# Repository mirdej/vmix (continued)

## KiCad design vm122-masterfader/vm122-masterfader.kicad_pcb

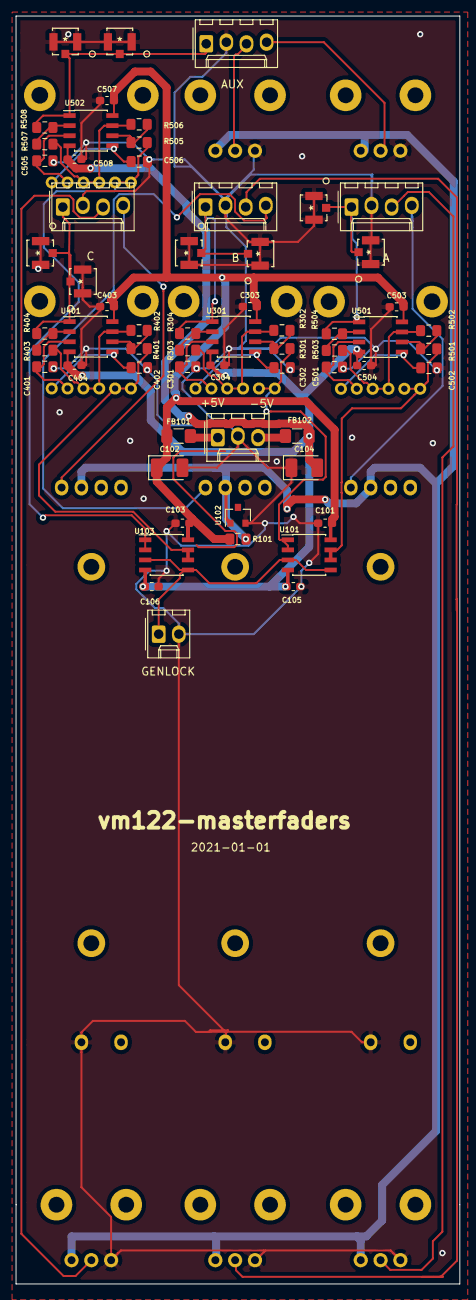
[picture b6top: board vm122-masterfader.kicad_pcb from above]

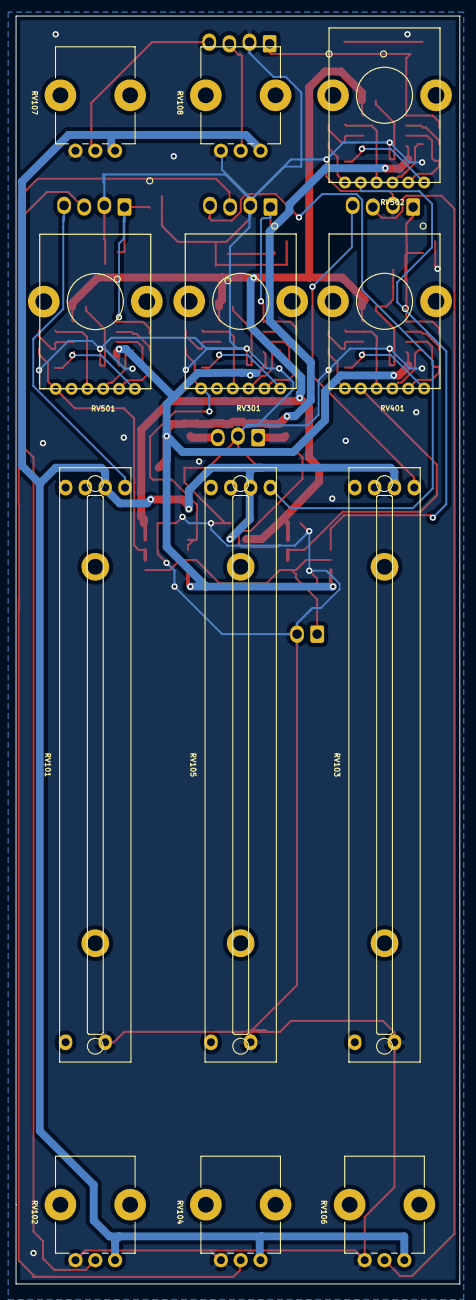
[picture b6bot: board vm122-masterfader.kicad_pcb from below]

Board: 2 copper layers, 56.0 x 160.0 mm, 74 parts (12 on the bottom side), 43 nets.

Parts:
C101, C103, C105, C106, C303, C304, C403, C404, C503, C504, C507, C508: 100n; C_0603_1608Metric_Pad1.05x0.95mm_HandSolder
C102, C104: CP; CP_EIA-3528-21_Kemet-B_Pad1.50x2.35mm_HandSolder
C301, C302, C401, C402, C501, C502, C505, C506: 10p; C_0805_2012Metric_Pad1.15x1.40mm_HandSolder
FB101, FB102: Ferrite_Bead; L_1206_3216Metric_Pad1.42x1.75mm_HandSolder
J101: Conn_01x03; Molex_KK-254_AE-6410-03A_1x03_P2.54mm_Vertical
J102: GENLOCK; Molex_KK-254_AE-6410-02A_1x02_P2.54mm_Vertical
J103: A; Molex_KK-254_AE-6410-04A_1x04_P2.54mm_Vertical
J104: B; Molex_KK-254_AE-6410-04A_1x04_P2.54mm_Vertical
J105: C; Molex_KK-254_AE-6410-04A_1x04_P2.54mm_Vertical
J106: D; Molex_KK-254_AE-6410-04A_1x04_P2.54mm_Vertical
J201, J202, J301, J302, J401, J402, J501, J502: UMCC; TE_UMCC_2337019-1
R101: 560; R_0805_2012Metric_Pad1.15x1.40mm_HandSolder
R301, R302, R303, R304, R401, R402, R403, R404, R501, R502, R503, R504, R505, R506, R507, R508: 220; R_0805_2012Metric_Pad1.15x1.40mm_HandSolder
RV101, RV103, RV105: SCALE; Potentiometer_Alps_RS6011xP_Slide
RV102, RV104, RV106, RV108: BIAS; Potentiometer_Alps_RK09K_Single_Vertical
RV107: SCALE; Potentiometer_Alps_RK09K_Single_Vertical
RV301, RV401, RV501, RV502: R_POT_Dual; RK12L123
U101, U103, U301, U401, U501, U502: LMH6643; SOIC-8_3.9x4.9mm_P1.27mm
U102: ADR510; SOT-23

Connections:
+5V: C101.1, C102.1, C103.1, C303.2, C403.2, C503.2, C507.2, FB101.1, R101.1, U101.8, U103.8, U301.8, U401.8, U501.8, U502.8
-5V: C104.2, C105.1, C106.1, C304.1, C404.1, C504.1, C508.1, FB102.1, U101.4, U103.4, U301.4, U401.4, U501.4, U502.4
/Phase1/INPUT: R501.2, RV501.1, RV501.2, U101.6, U101.7
/Phase1/OUTPUT: J103.1, J201.1, J202.1, R504.1, U501.1
/sheet5FF0F8E5/INPUT: R401.2, RV401.1, RV401.2, U103.6, U103.7
/sheet5FF0F8E5/OUTPUT: J105.1, J401.1, J402.1, R404.1, U401.1
/sheet5FF0F40B/INPUT: R301.2, RV301.1, RV301.2, U101.1, U101.2
/sheet5FF0F40B/OUTPUT: J104.1, J301.1, J302.1, R304.1, U301.1
/sheet5FF0F904/INPUT: R505.2, RV502.1, RV502.2, U103.1, U103.2
/sheet5FF0F904/OUTPUT: J106.1, J501.1, J502.1, R508.1, U502.1
GND: C101.2, C102.2, C103.2, C104.1, C105.2, C106.2, C301.2, C302.2, C303.1, C304.2, C401.2, C402.2, C403.1, C404.2, C501.2, C502.2, C503.1, C504.2, C505.2, C506.2, C507.1, C508.2, J101.2, J102.2, J103.2, J104.2, J105.2, J106.2, J201.2, J201.3, J202.2, J202.3, J301.2, J301.3, J302.2, J302.3, J401.2, J401.3, J402.2, J402.3, J501.2, J501.3, J502.2, J502.3, RV101.3, RV102.3, RV103.3, RV104.3, RV105.3, RV106.3, RV107.3, RV108.3, U102.2
unnamed: C301.1, RV301.6, U301.3
unnamed: C302.1, RV301.3, U301.5
unnamed: C401.1, RV401.6, U401.3
unnamed: C402.1, RV401.3, U401.5
unnamed: C501.1, RV501.6, U501.3
unnamed: C502.1, RV501.3, U501.5
unnamed: C505.1, RV502.6, U502.3
unnamed: C506.1, RV502.3, U502.5
unnamed: FB101.2, J101.1
unnamed: FB102.2, J101.3
unnamed: J102.1, U101.3, U101.5, U103.3, U103.5
unnamed: J103.3, RV102.2
unnamed: J103.4, RV101.2
unnamed: J104.3, RV104.2
unnamed: J104.4, RV105.2
unnamed: J105.3, RV106.2
unnamed: J105.4, RV103.2
unnamed: J106.3, RV108.2
unnamed: J106.4, RV107.2
unnamed: R301.1, R302.2, U301.6
unnamed: R302.1, R303.2, RV301.4, RV301.5, U301.7
unnamed: R303.1, R304.2, U301.2
unnamed: R401.1, R402.2, U401.6
unnamed: R402.1, R403.2, RV401.4, RV401.5, U401.7
unnamed: R403.1, R404.2, U401.2
unnamed: R501.1, R502.2, U501.6
unnamed: R502.1, R503.2, RV501.4, RV501.5, U501.7
unnamed: R503.1, R504.2, U501.2
unnamed: R505.1, R506.2, U502.6
unnamed: R506.1, R507.2, RV502.4, RV502.5, U502.7
unnamed: R507.1, R508.2, U502.2
VCCQ: R101.2, RV101.1, RV102.1, RV103.1, RV104.1, RV105.1, RV106.1, RV107.1, RV108.1, U102.1

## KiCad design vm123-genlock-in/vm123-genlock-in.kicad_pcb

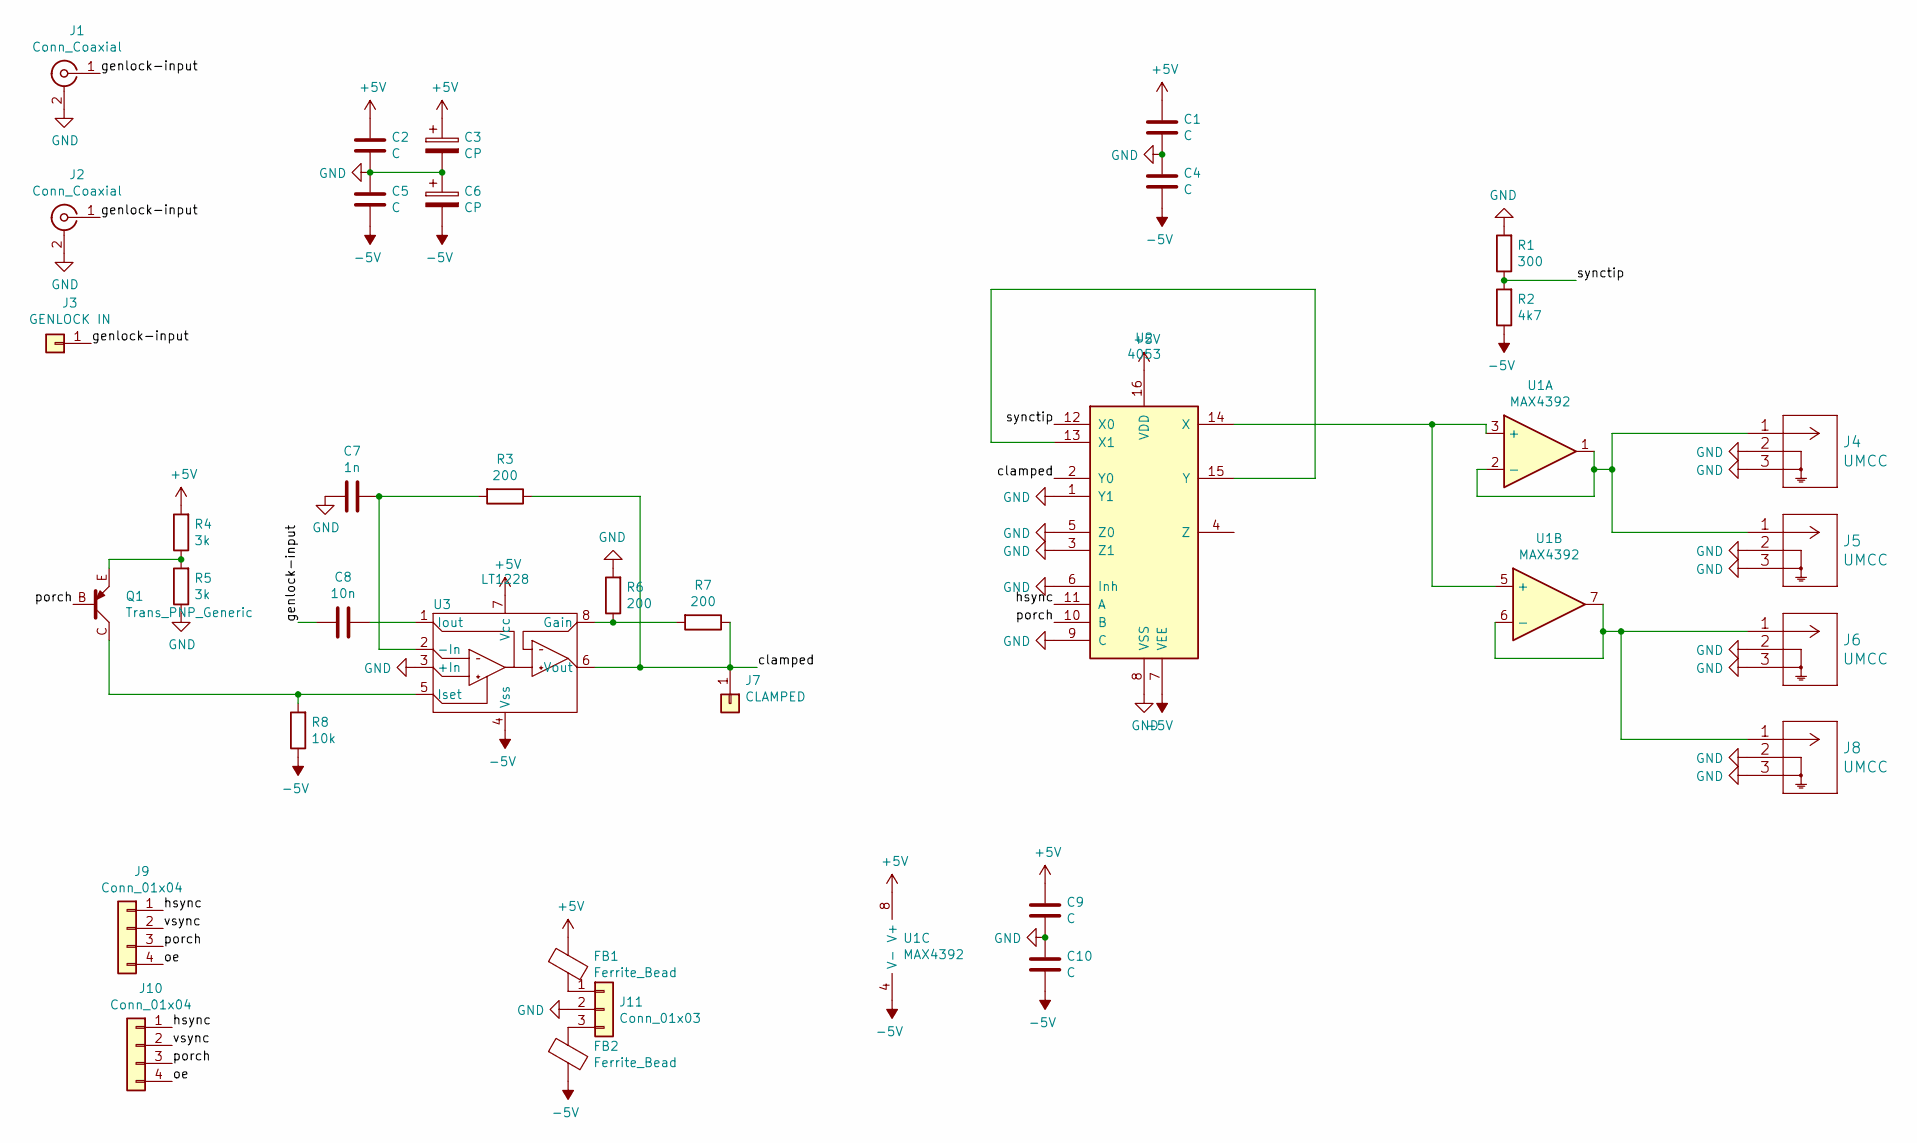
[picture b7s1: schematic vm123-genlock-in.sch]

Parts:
C1, C2, C4, C5, C9, C10: C; C_0603_1608Metric_Pad1.05x0.95mm_HandSolder
C3, C6: CP; CP_EIA-3528-21_Kemet-B_Pad1.50x2.35mm_HandSolder
C7: 1n; C_1206_3216Metric_Pad1.42x1.75mm_HandSolder
C8: 10n; C_1206_3216Metric_Pad1.42x1.75mm_HandSolder
FB1, FB2: Ferrite_Bead; L_1206_3216Metric_Pad1.42x1.75mm_HandSolder
J1, J2: Conn_Coaxial; BNC_MOLEX_0731000080_Horizontal
J3: GENLOCK IN; Solderpad_1mm
J4, J5, J6, J8: UMCC; TE_UMCC_2337019-1
J7: CLAMPED; Solderpad_1mm
J9, J10: Conn_01x04; Molex_KK-254_AE-6410-04A_1x04_P2.54mm_Vertical
J11: Conn_01x03; PinHeader_1x03_P2.54mm_Vertical
Q1: Trans_PNP_Generic; SOT-23_BEC
R1: 300; R_0805_2012Metric_Pad1.15x1.40mm_HandSolder
R2: 4k7; R_0805_2012Metric_Pad1.15x1.40mm_HandSolder
R3, R6, R7: 200; R_0805_2012Metric_Pad1.15x1.40mm_HandSolder
R4, R5: 3k; R_0805_2012Metric_Pad1.15x1.40mm_HandSolder
R8: 10k; R_0805_2012Metric_Pad1.15x1.40mm_HandSolder
U1: MAX4392; SOIC-8_3.9x4.9mm_P1.27mm
U2: 4053; SOIC-16_3.9x9.9mm_P1.27mm
U3: LT1228; SOIC-8_3.9x4.9mm_P1.27mm

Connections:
+5V: C1.1, C2.1, C3.1, C9.1, FB1.1, R4.2, U1.8 (V+), U2.16 (VDD), U3.7 (Vcc)
-5V: C4.2, C5.2, C6.2, C10.2, FB2.2, R2.1, R8.1, U1.4 (V-), U2.7 (VEE), U3.4 (Vss)
/clamped: J7.1, R3.1, R7.1, U2.2 (Y0), U3.6 (Vout)
/genlock-input: C8.2, J1.1 (In), J2.1 (In), J3.1
/hsync: J9.1, J10.1, U2.11 (A)
/oe: J9.4, J10.4
/porch: J9.3, J10.3, Q1.B, U2.10 (B)
/synctip: R1.1, R2.2, U2.12 (X0)
/vsync: J9.2, J10.2
GND: C1.2, C2.2, C3.2, C4.1, C5.1, C6.1, C7.2, C9.2, C10.1, J1.2 (Ext), J2.2 (Ext), J4.2, J4.3, J5.2, J5.3, J6.2, J6.3, J8.2, J8.3, J11.2, R1.2, R5.1, R6.2, U2.1 (Y1), U2.3 (Z1), U2.5 (Z0), U2.6 (Inh), U2.8 (VSS), U2.9 (C), U3.3 (+In)
unnamed: C7.1, R3.2, U3.2 (-In)
unnamed: C8.1, U3.1 (Iout)
unnamed: FB1.2, J11.1
unnamed: FB2.1, J11.3
unnamed: J4.1, J5.1, U1.1, U1.2 (-)
unnamed: J6.1, J8.1, U1.6 (-), U1.7
unnamed: Q1.C, R8.2, U3.5 (Iset)
unnamed: Q1.E, R4.1, R5.2
unnamed: R6.1, R7.2, U3.8 (Gain)
unnamed: U1.3 (+), U1.5 (+), U2.14 (X)
unnamed: U2.13 (X1), U2.15 (Y)

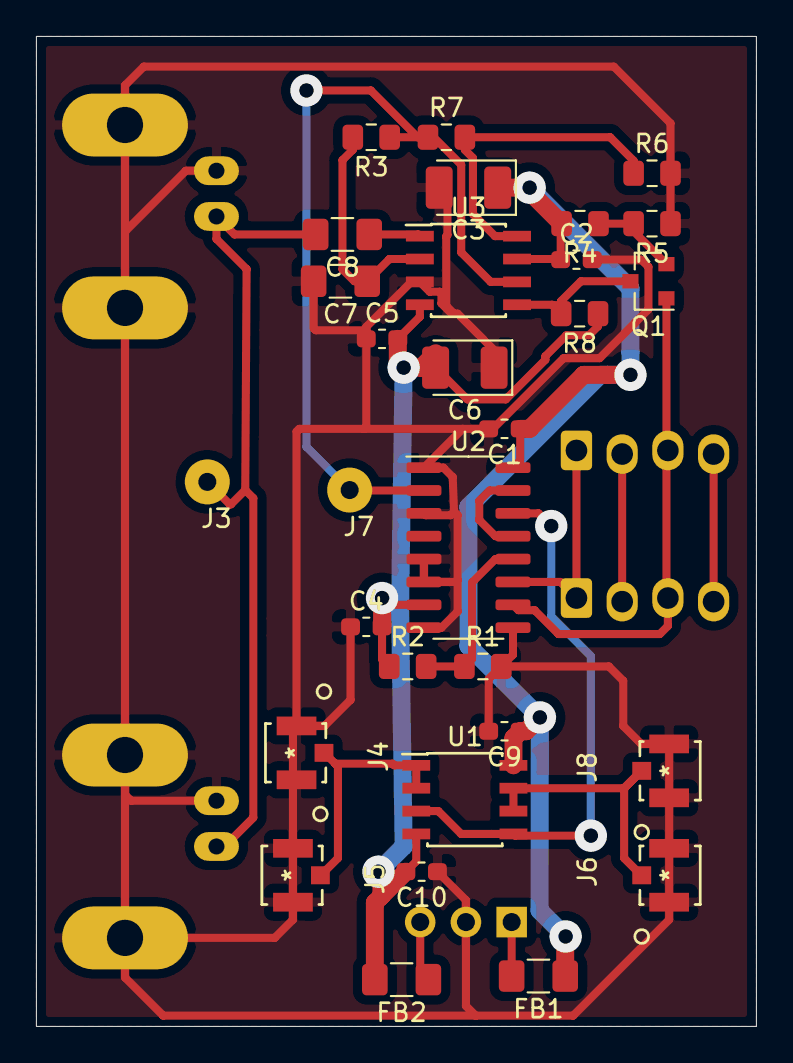
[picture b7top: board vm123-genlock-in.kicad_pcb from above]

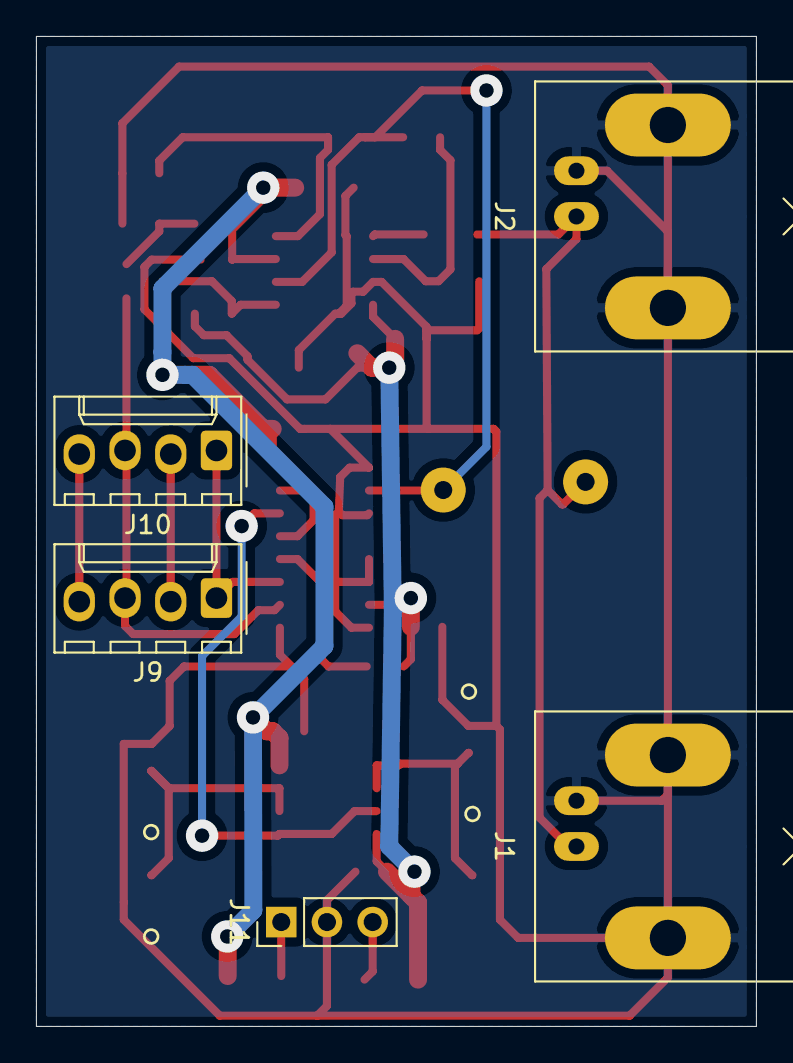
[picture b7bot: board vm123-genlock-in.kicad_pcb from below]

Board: 2 copper layers, 40.0 x 55.0 mm, 35 parts (5 on the bottom side), 21 nets.

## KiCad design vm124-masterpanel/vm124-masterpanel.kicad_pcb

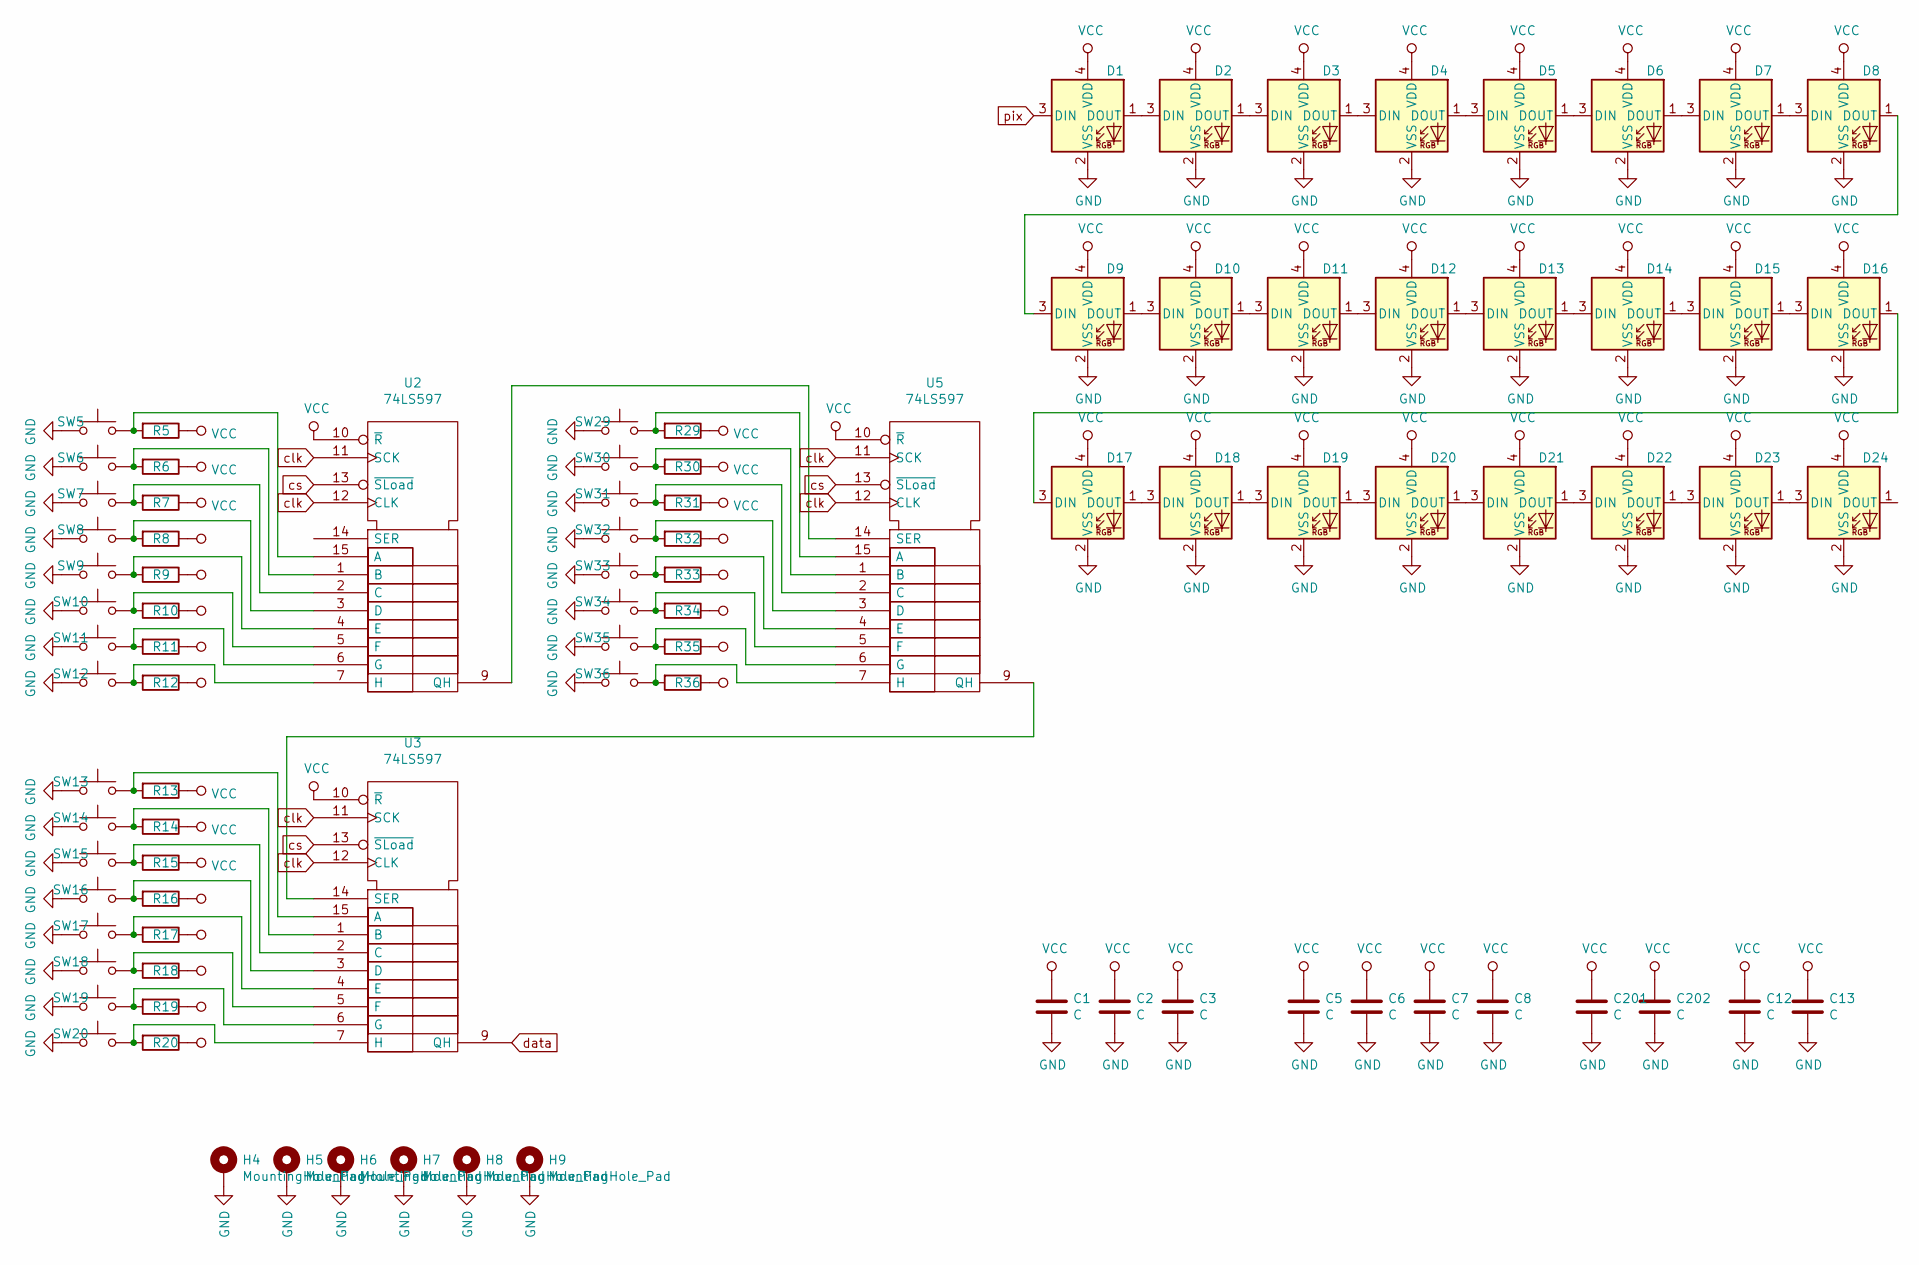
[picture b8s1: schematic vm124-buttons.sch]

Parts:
C1, C2, C3, C5, C6, C7, C8, C12, C13, C201, C202: C; C_0603_1608Metric_Pad1.05x0.95mm_HandSolder
D1, D2, D3, D4, D5, D6, D7, D8, D9, D10, D11, D12, D13, D14, D15, D16, D17, D18, D19, D20, D21, D22, D23, D24: SK6812MINI; LED_SK6812MINI_PLCC4_3.5x3.5mm_P1.75mm
H4, H5, H6, H7, H8, H9: MountingHole_Pad; MountingHole_3.2mm_M3_DIN965_Pad
R5, R6, R7, R8, R9, R10, R11, R12, R13, R14, R15, R16, R17, R18, R19, R20, R29, R30, R31, R32, R33, R34, R35, R36: R; R_0805_2012Metric_Pad1.15x1.40mm_HandSolder
SW5, SW6, SW7, SW8, SW9, SW10, SW11, SW12, SW13, SW14, SW15, SW16, SW17, SW18, SW19, SW20, SW29, SW30, SW31, SW32, SW33, SW34, SW35, SW36: SW_Push; Alps_Tactile_Switch
U2, U3, U5: 74LS597; SOP-16_4.4x10.4mm_P1.27mm

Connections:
GND: C1.2, C2.2, C3.2, C5.2, C6.2, C7.2, C8.2, C12.2, C13.2, C201.2, C202.2, D1.2 (VSS), D2.2 (VSS), D3.2 (VSS), D4.2 (VSS), D5.2 (VSS), D6.2 (VSS), D7.2 (VSS), D8.2 (VSS), D9.2 (VSS), D10.2 (VSS), D11.2 (VSS), D12.2 (VSS), D13.2 (VSS), D14.2 (VSS), D15.2 (VSS), D16.2 (VSS), D17.2 (VSS), D18.2 (VSS), D19.2 (VSS), D20.2 (VSS), D21.2 (VSS), D22.2 (VSS), D23.2 (VSS), D24.2 (VSS), H4.1, H5.1, H6.1, H7.1, H8.1, H9.1, SW5.1, SW6.1, SW7.1, SW8.1, SW9.1, SW10.1, SW11.1, SW12.1, SW13.1, SW14.1, SW15.1, SW16.1, SW17.1, SW18.1, SW19.1, SW20.1, SW29.1, SW30.1, SW31.1, SW32.1, SW33.1, SW34.1, SW35.1, SW36.1, U2.8 (GND), U3.8 (GND), U5.8 (GND); also elsewhere on the board
unnamed: D1.1 (DOUT), D2.3 (DIN)
unnamed: D2.1 (DOUT), D3.3 (DIN)
unnamed: D3.1 (DOUT), D4.3 (DIN)
unnamed: D4.1 (DOUT), D5.3 (DIN)
unnamed: D5.1 (DOUT), D6.3 (DIN)
unnamed: D6.1 (DOUT), D7.3 (DIN)
unnamed: D7.1 (DOUT), D8.3 (DIN)
unnamed: D8.1 (DOUT), D9.3 (DIN)
unnamed: D10.1 (DOUT), D11.3 (DIN)
unnamed: D9.1 (DOUT), D10.3 (DIN)
unnamed: D11.1 (DOUT), D12.3 (DIN)
unnamed: D12.1 (DOUT), D13.3 (DIN)
unnamed: D13.1 (DOUT), D14.3 (DIN)
unnamed: D14.1 (DOUT), D15.3 (DIN)
unnamed: D15.1 (DOUT), D16.3 (DIN)
unnamed: D16.1 (DOUT), D17.3 (DIN)
unnamed: D17.1 (DOUT), D18.3 (DIN)
unnamed: D18.1 (DOUT), D19.3 (DIN)
unnamed: D19.1 (DOUT), D20.3 (DIN)
unnamed: D20.1 (DOUT), D21.3 (DIN)
unnamed: D21.1 (DOUT), D22.3 (DIN)
unnamed: D22.1 (DOUT), D23.3 (DIN)
unnamed: D23.1 (DOUT), D24.3 (DIN)
unnamed: R5.2, SW5.2, U2.15 (A)
unnamed: R6.2, SW6.2, U2.1 (B)
unnamed: R7.2, SW7.2, U2.2 (C)
unnamed: R8.2, SW8.2, U2.3 (D)
unnamed: R9.2, SW9.2, U2.4 (E)
unnamed: R10.2, SW10.2, U2.5 (F)
unnamed: R11.2, SW11.2, U2.6 (G)
unnamed: R12.2, SW12.2, U2.7 (H)
unnamed: R13.2, SW13.2, U3.15 (A)
unnamed: R14.2, SW14.2, U3.1 (B)
unnamed: R15.2, SW15.2, U3.2 (C)
unnamed: R16.2, SW16.2, U3.3 (D)
unnamed: R17.2, SW17.2, U3.4 (E)
unnamed: R18.2, SW18.2, U3.5 (F)
unnamed: R19.2, SW19.2, U3.6 (G)
unnamed: R20.2, SW20.2, U3.7 (H)
unnamed: R29.2, SW29.2, U5.15 (A)
unnamed: R30.2, SW30.2, U5.1 (B)
unnamed: R31.2, SW31.2, U5.2 (C)
unnamed: R32.2, SW32.2, U5.3 (D)
unnamed: R33.2, SW33.2, U5.4 (E)
unnamed: R34.2, SW34.2, U5.5 (F)
unnamed: R35.2, SW35.2, U5.6 (G)
unnamed: R36.2, SW36.2, U5.7 (H)
unnamed: U2.9 (QH), U5.14 (SER)
unnamed: U3.14 (SER), U5.9 (QH)
VCC: C1.1, C2.1, C3.1, C5.1, C6.1, C7.1, C8.1, C12.1, C13.1, C201.1, C202.1, D1.4 (VDD), D2.4 (VDD), D3.4 (VDD), D4.4 (VDD), D5.4 (VDD), D6.4 (VDD), D7.4 (VDD), D8.4 (VDD), D9.4 (VDD), D10.4 (VDD), D11.4 (VDD), D12.4 (VDD), D13.4 (VDD), D14.4 (VDD), D15.4 (VDD), D16.4 (VDD), D17.4 (VDD), D18.4 (VDD), D19.4 (VDD), D20.4 (VDD), D21.4 (VDD), D22.4 (VDD), D23.4 (VDD), D24.4 (VDD), R5.1, R6.1, R7.1, R8.1, R9.1, R10.1, R11.1, R12.1, R13.1, R14.1, R15.1, R16.1, R17.1, R18.1, R19.1, R20.1, R29.1, R30.1, R31.1, R32.1, R33.1, R34.1, R35.1, R36.1, U2.10 (~R), U2.16 (VCC), U3.10 (~R), U3.16 (VCC), U5.10 (~R), U5.16 (VCC); also elsewhere on the board
clk: U2.11 (SCK), U2.12 (CLK), U3.11 (SCK), U3.12 (CLK), U5.11 (SCK), U5.12 (CLK); also elsewhere on the board
cs: U2.13 (~SLoad), U3.13 (~SLoad), U5.13 (~SLoad); also elsewhere on the board
data: U3.9 (QH); also elsewhere on the board
pix: D1.3 (DIN); also elsewhere on the board

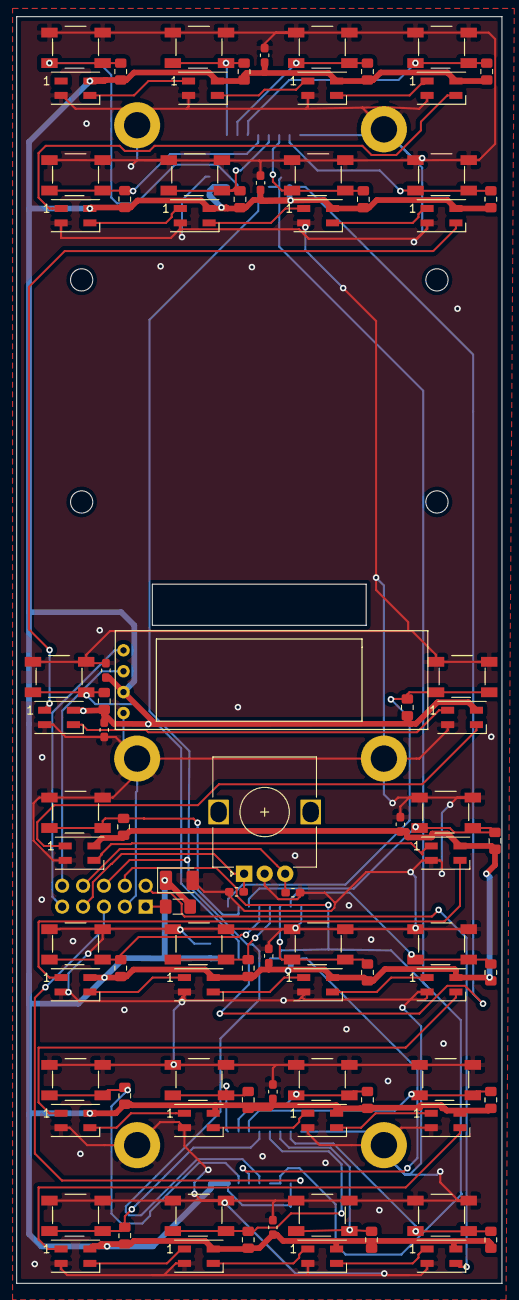
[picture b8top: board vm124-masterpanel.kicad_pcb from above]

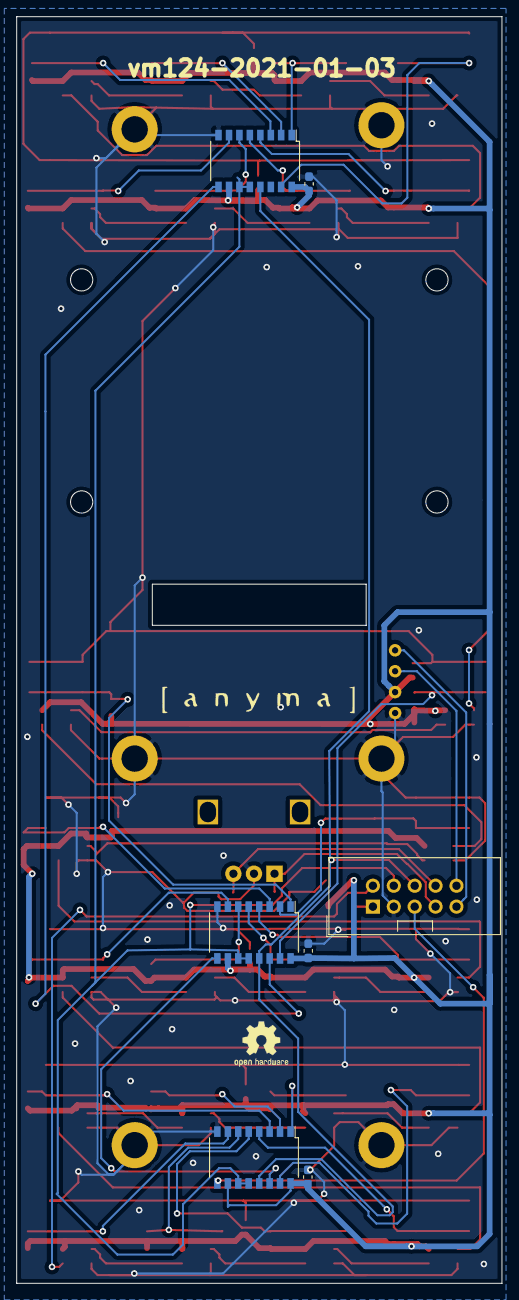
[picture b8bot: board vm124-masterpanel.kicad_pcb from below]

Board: 2 copper layers, 59.0 x 154.0 mm, 105 parts (9 on the bottom side), 60 nets.

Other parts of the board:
C101: CP; CP_EIA-3528-21_Kemet-B_Pad1.50x2.35mm_HandSolder
C102, C103: 100n; C_0603_1608Metric_Pad1.05x0.95mm_HandSolder
FB101: Ferrite_Bead; L_1206_3216Metric_Pad1.42x1.75mm_HandSolder
H101, H102, H103, H104: MountingHole; MountingHole_2.7mm_M2.5
J101: Display; Bangood-OLED-128x32
J102: To-CPU; IDC-Header_2x05_P2.54mm_Vertical
SW101: Rotary_Encoder; RotaryEncoder_Alps_EC12E_Vertical_H20mm
U101: LOGO; logo_anyma
U102: LOGO; OSHW-Logo2_7.3x6mm_SilkScreen

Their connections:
/enc_a: C102.1, J102.7, SW101.A
/enc_b: C103.1, J102.8, SW101.B
/scl: J101.3, J102.10
/sda: J101.4, J102.9
GND: C101.2, C102.2, C103.2, J101.1, J102.3, SW101.C; also elsewhere on the board
unnamed: FB101.2, J102.1
VCC: C101.1, FB101.1, J101.2; also elsewhere on the board
clk: J102.4; also elsewhere on the board
cs: J102.6; also elsewhere on the board
data: J102.5; also elsewhere on the board
pix: J102.2; also elsewhere on the board
